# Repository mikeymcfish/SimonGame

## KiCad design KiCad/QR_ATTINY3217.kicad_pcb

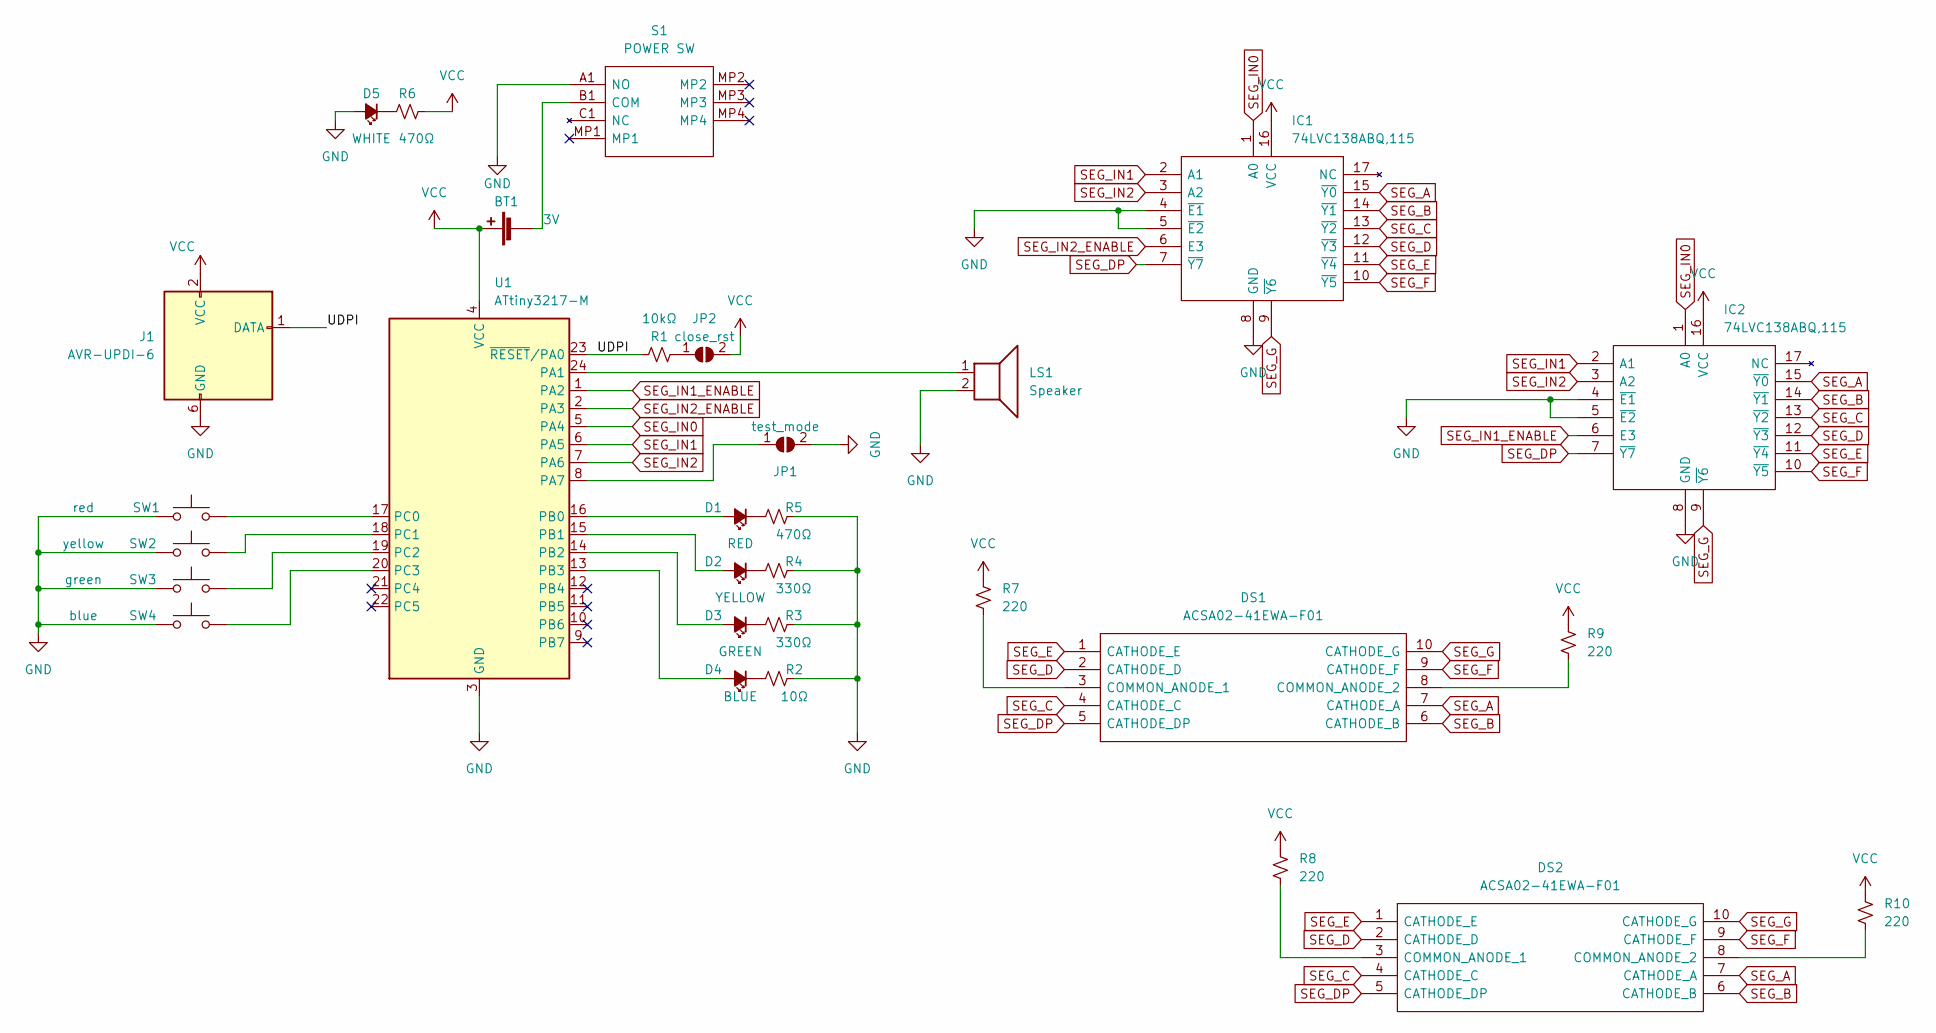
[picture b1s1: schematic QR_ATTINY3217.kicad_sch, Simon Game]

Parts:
BT1: 3V; SMTU2032LF
D1: RED; LED_1206_3216Metric_Pad1.42x1.75mm_HandSolder
D2: YELLOW; LED_1206_3216Metric_Pad1.42x1.75mm_HandSolder
D3: GREEN; LED_1206_3216Metric_Pad1.42x1.75mm_HandSolder
D4: BLUE; LED_1206_3216Metric_Pad1.42x1.75mm_HandSolder
D5: WHITE; LED_1206_3216Metric_Pad1.42x1.75mm_HandSolder
DS1, DS2: ACSA02-41EWA-F01; ACSA0241EWAF01; Mouser Part Number 604-ACSA02-41EWA
IC1, IC2: 74LVC138ABQ,115; 74AHCT595BQ115; Mouser Part Number 771-LVC138ABQ115
J1: AVR-UPDI-6; PinHeader_2x03_P2.54mm_Horizontal
JP1: test_mode; SolderJumper-2_P1.3mm_Open_Pad1.0x1.5mm
JP2: close_rst; SolderJumper-2_P1.3mm_Open_Pad1.0x1.5mm
LS1: Speaker; CPT111783SMTTR
R1: 10kΩ; R_1206_3216Metric_Pad1.30x1.75mm_HandSolder
R2: 10Ω; R_1206_3216Metric_Pad1.30x1.75mm_HandSolder
R3, R4: 330Ω; R_1206_3216Metric_Pad1.30x1.75mm_HandSolder
R5, R6: 470Ω; R_1206_3216Metric_Pad1.30x1.75mm_HandSolder
R7, R8, R9, R10: 220; R_1206_3216Metric
S1: POWER SW; MSS3VTR; Mouser Part Number 113-MSS3-V-T/R
SW1: red; FSM4JSMATR
SW2: yellow; FSM4JSMATR
SW3: green; FSM4JSMATR
SW4: blue; FSM4JSMATR
U1: ATtiny3217-M; QFN-24-1EP_4x4mm_P0.5mm_EP2.6x2.6mm

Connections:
/UDPI: J1.1 (DATA), R1.2, U1.23 (~RESET/PA0)
GND: D5.2 (A), IC1.4 (~E1), IC1.5 (~E2), IC1.8 (GND), IC2.4 (~E1), IC2.5 (~E2), IC2.8 (GND), J1.6 (GND), JP1.2 (B), LS1.2, R2.1, R3.2, R4.2, R5.2, S1.A1 (NO), SW1.4 (1), SW2.4 (1), SW3.4 (1), SW4.4 (1), U1.3 (GND), U1.25 (GND)
unnamed: BT1.2 (-), S1.B1 (COM)
unnamed: D1.1 (K), R5.1
unnamed: D1.2 (A), U1.16 (PB0)
unnamed: D2.1 (K), R4.1
unnamed: D2.2 (A), U1.15 (PB1)
unnamed: D3.1 (K), R3.1
unnamed: D3.2 (A), U1.14 (PB2)
unnamed: D4.1 (K), R2.2
unnamed: D4.2 (A), U1.13 (PB3)
unnamed: D5.1 (K), R6.2
unnamed: DS1.3 (COMMON_ANODE_1), R7.2
unnamed: DS1.8 (COMMON_ANODE_2), R9.2
unnamed: DS2.3 (COMMON_ANODE_1), R8.2
unnamed: DS2.8 (COMMON_ANODE_2), R10.2
unnamed: JP1.1 (A), U1.8 (PA7)
unnamed: JP2.1 (A), R1.1
unnamed: LS1.1, U1.24 (PA1)
unnamed: SW1.1, U1.17 (PC0)
unnamed: SW2.1 (2), U1.18 (PC1)
unnamed: SW3.1 (2), U1.19 (PC2)
unnamed: SW4.1 (2), U1.20 (PC3)
SEG_A: DS1.7 (CATHODE_A), DS2.7 (CATHODE_A), IC1.15 (~Y0), IC2.15 (~Y0)
SEG_B: DS1.6 (CATHODE_B), DS2.6 (CATHODE_B), IC1.14 (~Y1), IC2.14 (~Y1)
SEG_C: DS1.4 (CATHODE_C), DS2.4 (CATHODE_C), IC1.13 (~Y2), IC2.13 (~Y2)
SEG_D: DS1.2 (CATHODE_D), DS2.2 (CATHODE_D), IC1.12 (~Y3), IC2.12 (~Y3)
SEG_DP: DS1.5 (CATHODE_DP), DS2.5 (CATHODE_DP), IC1.7 (~Y7), IC2.7 (~Y7)
SEG_E: DS1.1 (CATHODE_E), DS2.1 (CATHODE_E), IC1.11 (~Y4), IC2.11 (~Y4)
SEG_F: DS1.9 (CATHODE_F), DS2.9 (CATHODE_F), IC1.10 (~Y5), IC2.10 (~Y5)
SEG_G: DS1.10 (CATHODE_G), DS2.10 (CATHODE_G), IC1.9 (~Y6), IC2.9 (~Y6)
SEG_IN0: IC1.1 (A0), IC2.1 (A0), U1.5 (PA4)
SEG_IN1: IC1.2 (A1), IC2.2 (A1), U1.6 (PA5)
SEG_IN1_ENABLE: IC2.6 (E3), U1.1 (PA2)
SEG_IN2: IC1.3 (A2), IC2.3 (A2), U1.7 (PA6)
SEG_IN2_ENABLE: IC1.6 (E3), U1.2 (PA3)
VCC: BT1.1 (+), IC1.16 (VCC), IC2.16 (VCC), J1.2 (VCC), JP2.2 (B), R6.1, R7.1, R8.1, R9.1, R10.1, U1.4 (VCC)

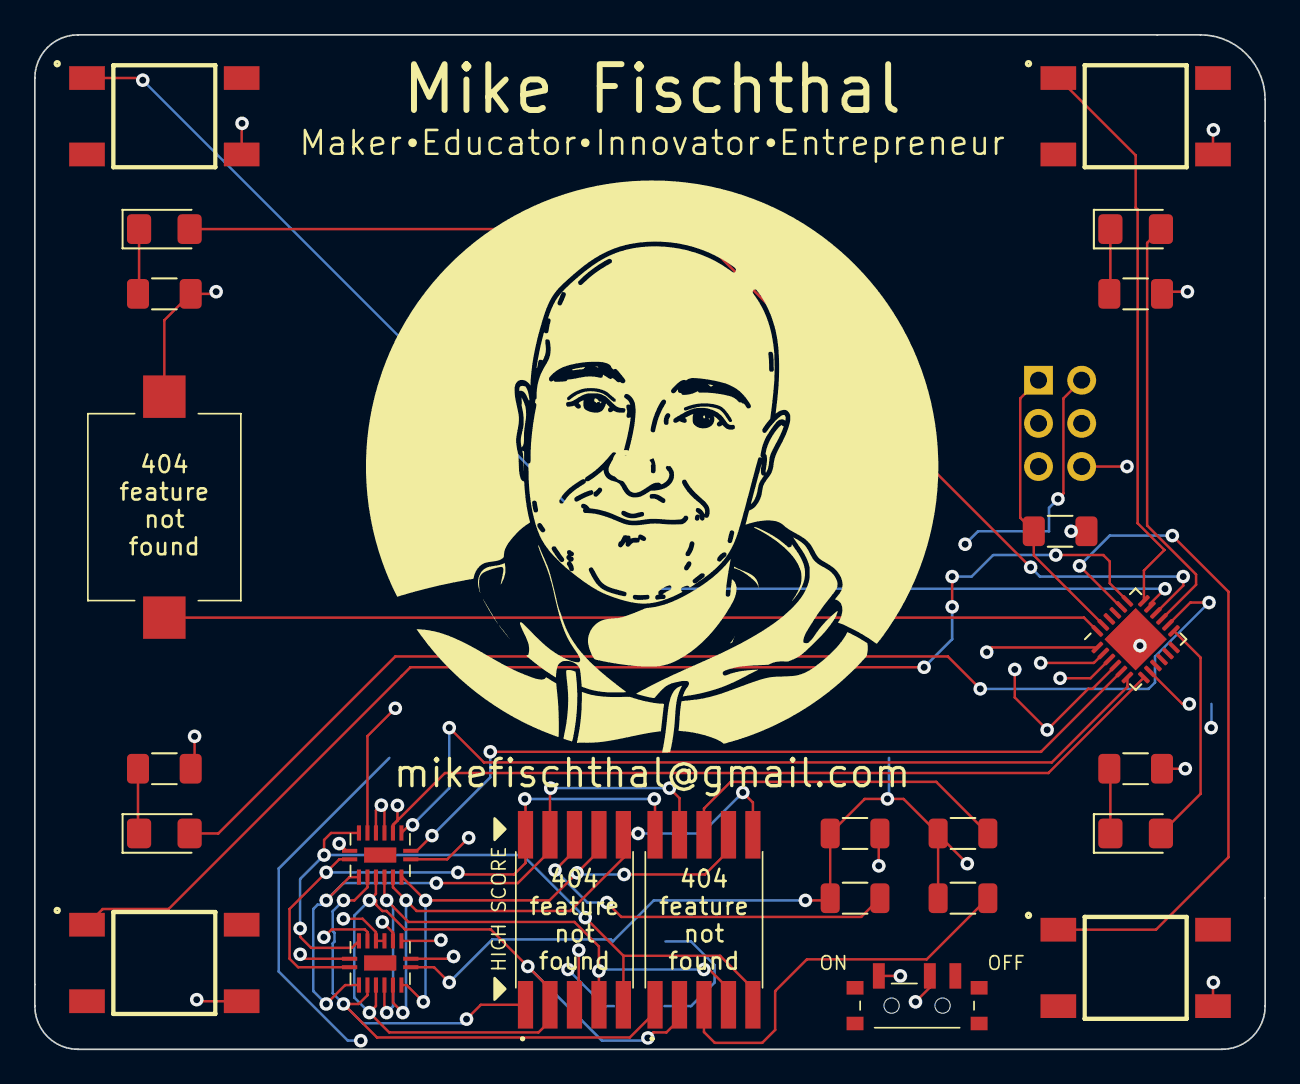
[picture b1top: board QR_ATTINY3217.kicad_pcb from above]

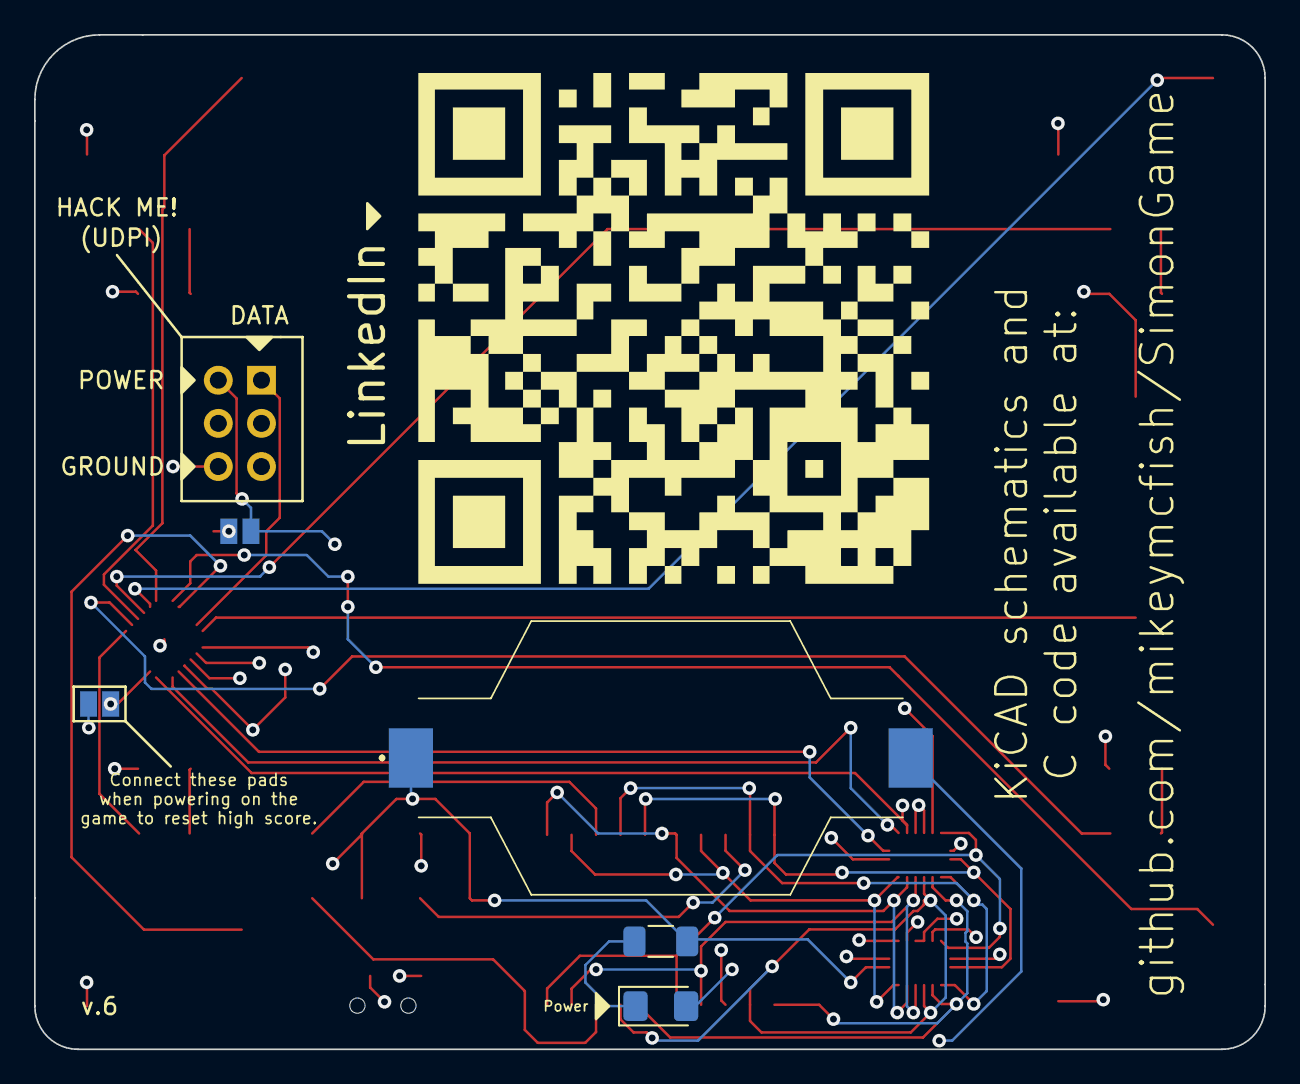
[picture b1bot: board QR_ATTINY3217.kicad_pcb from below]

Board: 4 copper layers, 72.4 x 59.7 mm, 30 parts (5 on the bottom side), 37 nets.

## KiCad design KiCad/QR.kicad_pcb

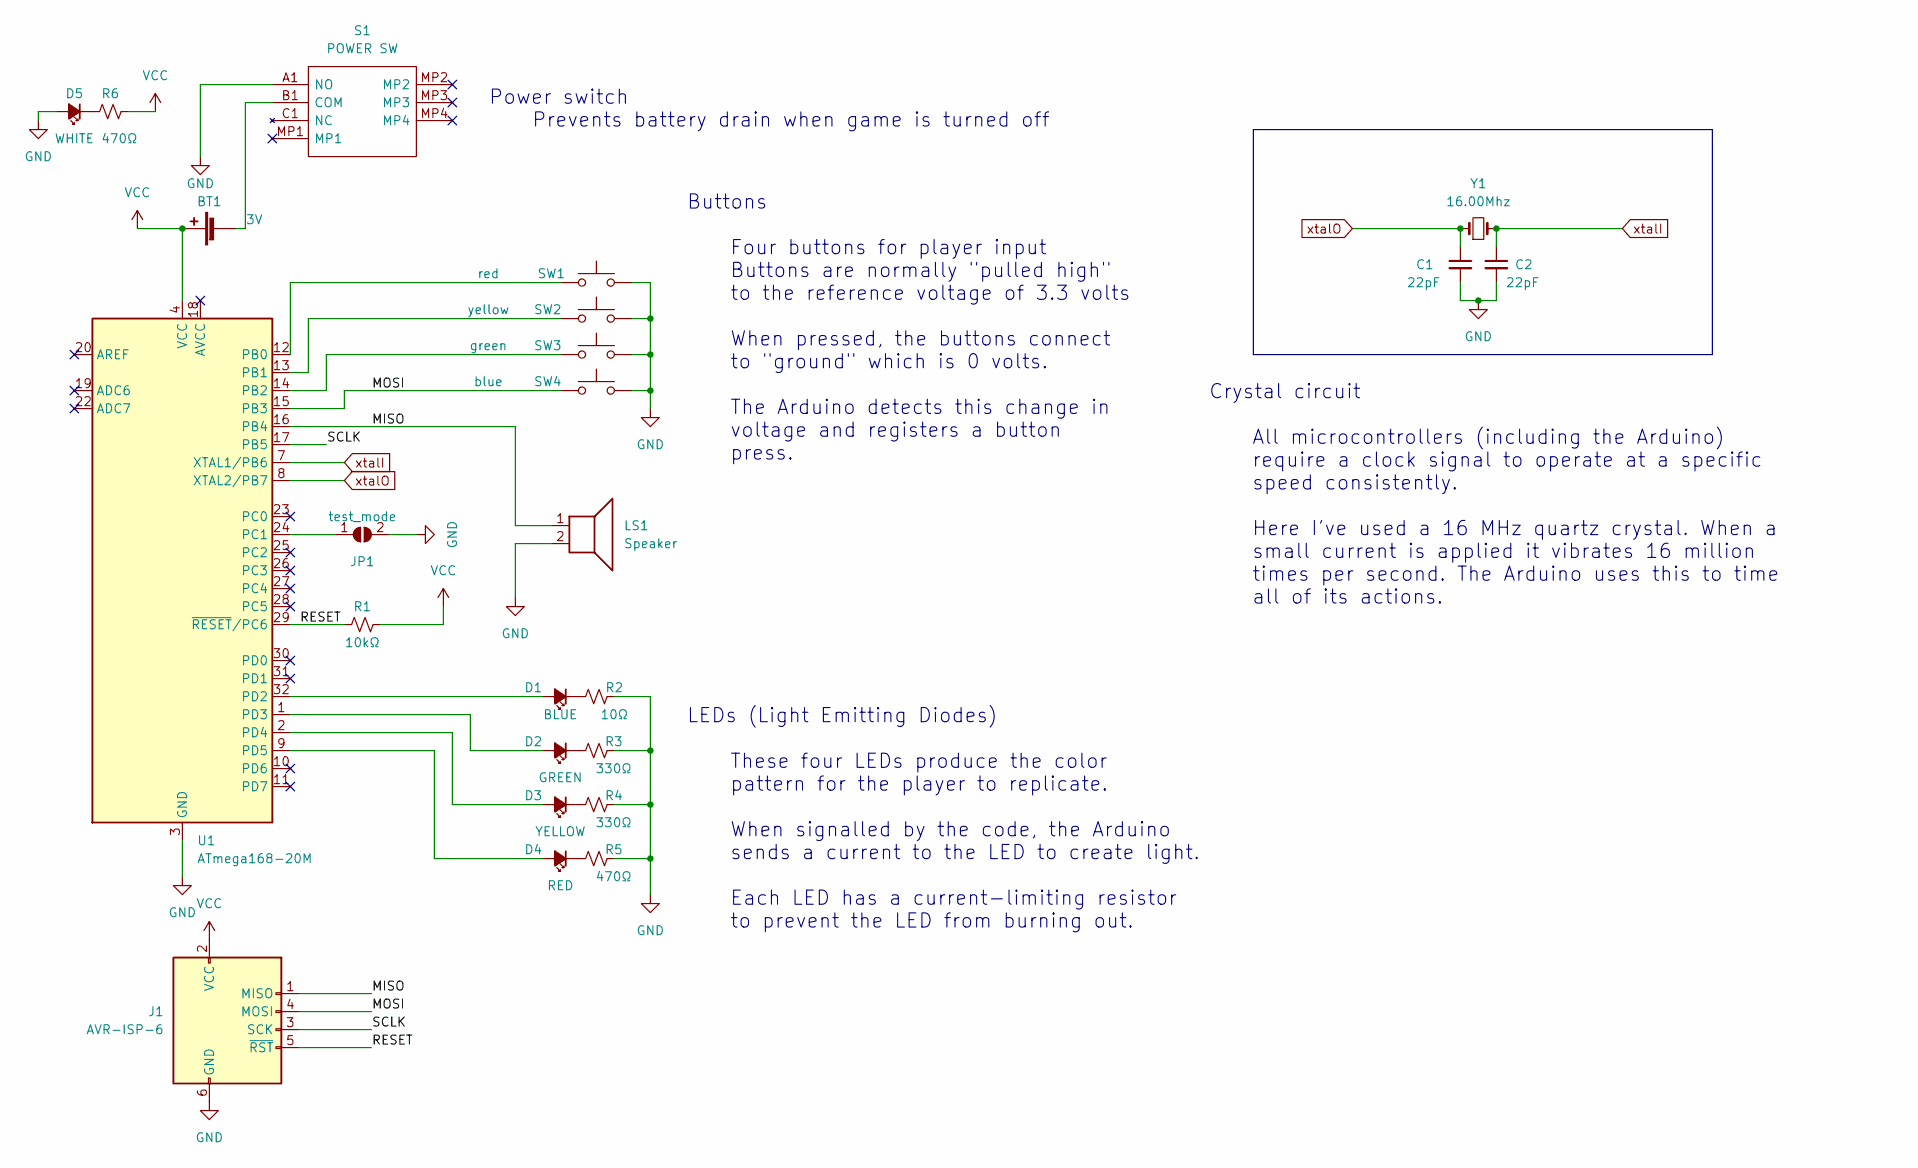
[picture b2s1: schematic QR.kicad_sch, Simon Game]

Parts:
BT1: 3V; SMTU2032LF
C1, C2: 22pF; C_1206_3216Metric_Pad1.33x1.80mm_HandSolder
D1: BLUE; LED_1206_3216Metric_Pad1.42x1.75mm_HandSolder
D2: GREEN; LED_1206_3216Metric_Pad1.42x1.75mm_HandSolder
D3: YELLOW; LED_1206_3216Metric_Pad1.42x1.75mm_HandSolder
D4: RED; LED_1206_3216Metric_Pad1.42x1.75mm_HandSolder
D5: WHITE; LED_1206_3216Metric_Pad1.42x1.75mm_HandSolder
J1: AVR-ISP-6; PinHeader_2x03_P2.54mm_Horizontal
JP1: test_mode; SolderJumper-2_P1.3mm_Open_Pad1.0x1.5mm
LS1: Speaker; CPT111783SMTTR
R1: 10kΩ; R_1206_3216Metric_Pad1.30x1.75mm_HandSolder
R2: 10Ω; R_1206_3216Metric_Pad1.30x1.75mm_HandSolder
R3, R4: 330Ω; R_1206_3216Metric_Pad1.30x1.75mm_HandSolder
R5, R6: 470Ω; R_1206_3216Metric_Pad1.30x1.75mm_HandSolder
S1: POWER SW; MSS3VTR; Mouser Part Number 113-MSS3-V-T/R
SW1: red; FSM4JSMATR
SW2: yellow; FSM4JSMATR
SW3: green; FSM4JSMATR
SW4: blue; FSM4JSMATR
U1: ATmega168-20M; QFN-32-1EP_5x5mm_P0.5mm_EP3.1x3.1mm
Y1: 16.00Mhz; Crystal_SMD_HC49-SD_HandSoldering

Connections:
/MISO: J1.1 (MISO), LS1.1, U1.16 (PB4)
/MOSI: J1.4 (MOSI), SW4.1, U1.15 (PB3)
/RESET: J1.5 (~RST), R1.2, U1.29 (~RESET/PC6)
/SCLK: J1.3 (SCK), U1.17 (PB5)
GND: C1.2, C2.2, D5.2 (A), J1.6 (GND), JP1.2 (B), LS1.2, R2.1, R3.2, R4.2, R5.2, S1.A1 (NO), SW1.4 (2), SW2.4 (2), SW3.4 (2), SW4.4 (2), U1.3 (GND), U1.5 (GND), U1.21 (GND), U1.33 (GND); also elsewhere on the board
unnamed: BT1.2 (-), S1.B1 (COM)
unnamed: D1.1 (K), R2.2
unnamed: D1.2 (A), U1.32 (PD2)
unnamed: D2.1 (K), R3.1
unnamed: D2.2 (A), U1.1 (PD3)
unnamed: D3.1 (K), R4.1
unnamed: D3.2 (A), U1.2 (PD4)
unnamed: D4.1 (K), R5.1
unnamed: D4.2 (A), U1.9 (PD5)
unnamed: D5.1 (K), R6.2
unnamed: SW1.1, U1.12 (PB0)
unnamed: SW2.1, U1.13 (PB1)
unnamed: SW3.1, U1.14 (PB2)
unnamed 18: JP1.1 (A), U1.24 (PC1); also elsewhere on the board
VCC: BT1.1 (+), J1.2 (VCC), R1.1, R6.1, U1.4 (VCC), U1.6 (VCC)
xtalI: C2.1, U1.7 (XTAL1/PB6), Y1.2
xtalO: C1.1, U1.8 (XTAL2/PB7), Y1.1

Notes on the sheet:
Buttons Four buttons for player input Buttons are normally "pulled high" to the reference voltage of 3.3 volts When pressed, the buttons connect to "ground" which is 0 volts. The Arduino detects this change in voltage and registers a button press.
LEDs (Light Emitting Diodes) These four LEDs produce the color pattern for the player to replicate. When signalled by the code, the Arduino sends a current to the LED to create light. Each LED has a current-limiting resistor to prevent the LED from burning out.
Power switch Prevents battery drain when game is turned off
Crystal circuit All microcontrollers (including the Arduino) require a clock signal to operate at a specific speed consistently. Here I've used a 16 MHz quartz crystal. When a small current is applied it vibrates 16 million times per second. The Arduino uses this to time all of its actions.

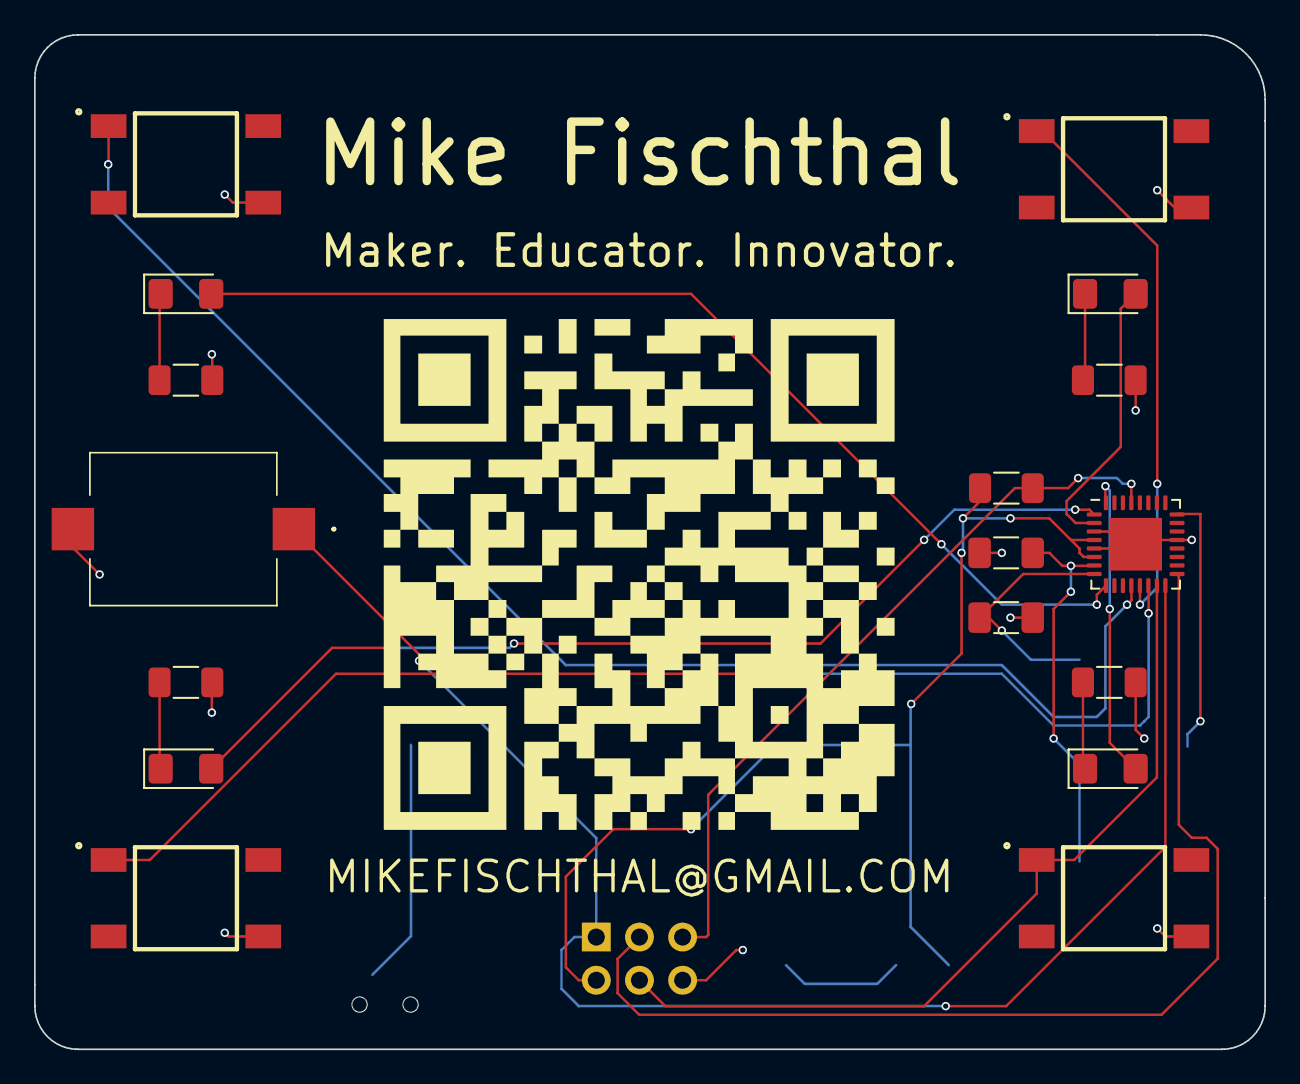
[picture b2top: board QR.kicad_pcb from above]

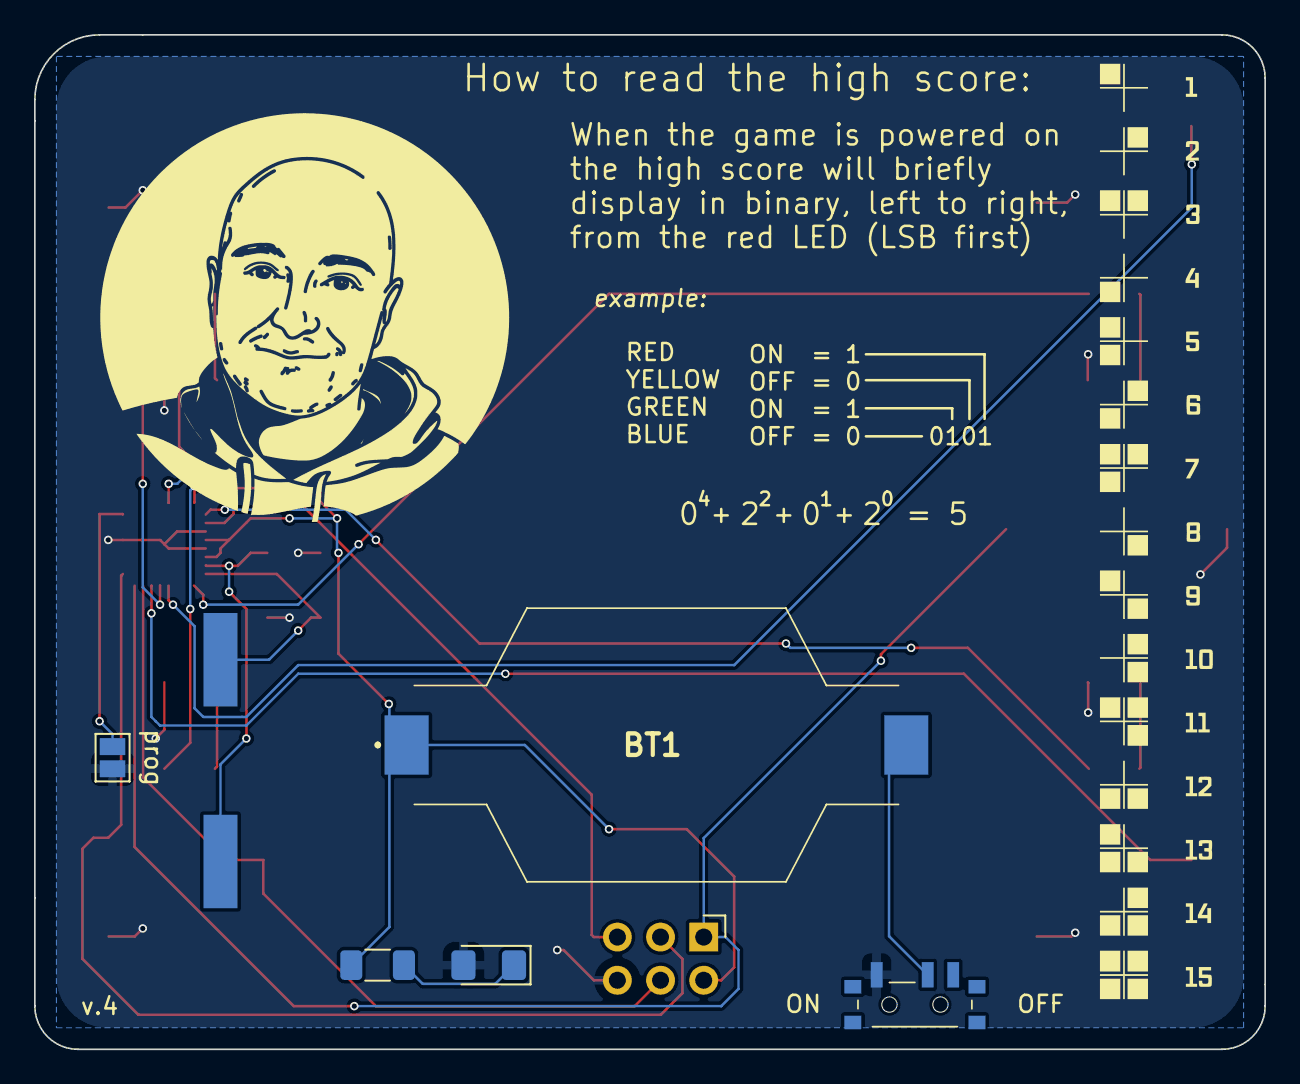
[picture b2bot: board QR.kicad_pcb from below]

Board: 2 copper layers, 72.4 x 59.7 mm, 24 parts (7 on the bottom side), 22 nets.

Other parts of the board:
prog: test_mode; SolderJumper-2_P1.3mm_Open_Pad1.0x1.5mm

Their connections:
GND: prog.2 (B); also elsewhere on the board
unnamed 18: prog.1 (A); also elsewhere on the board

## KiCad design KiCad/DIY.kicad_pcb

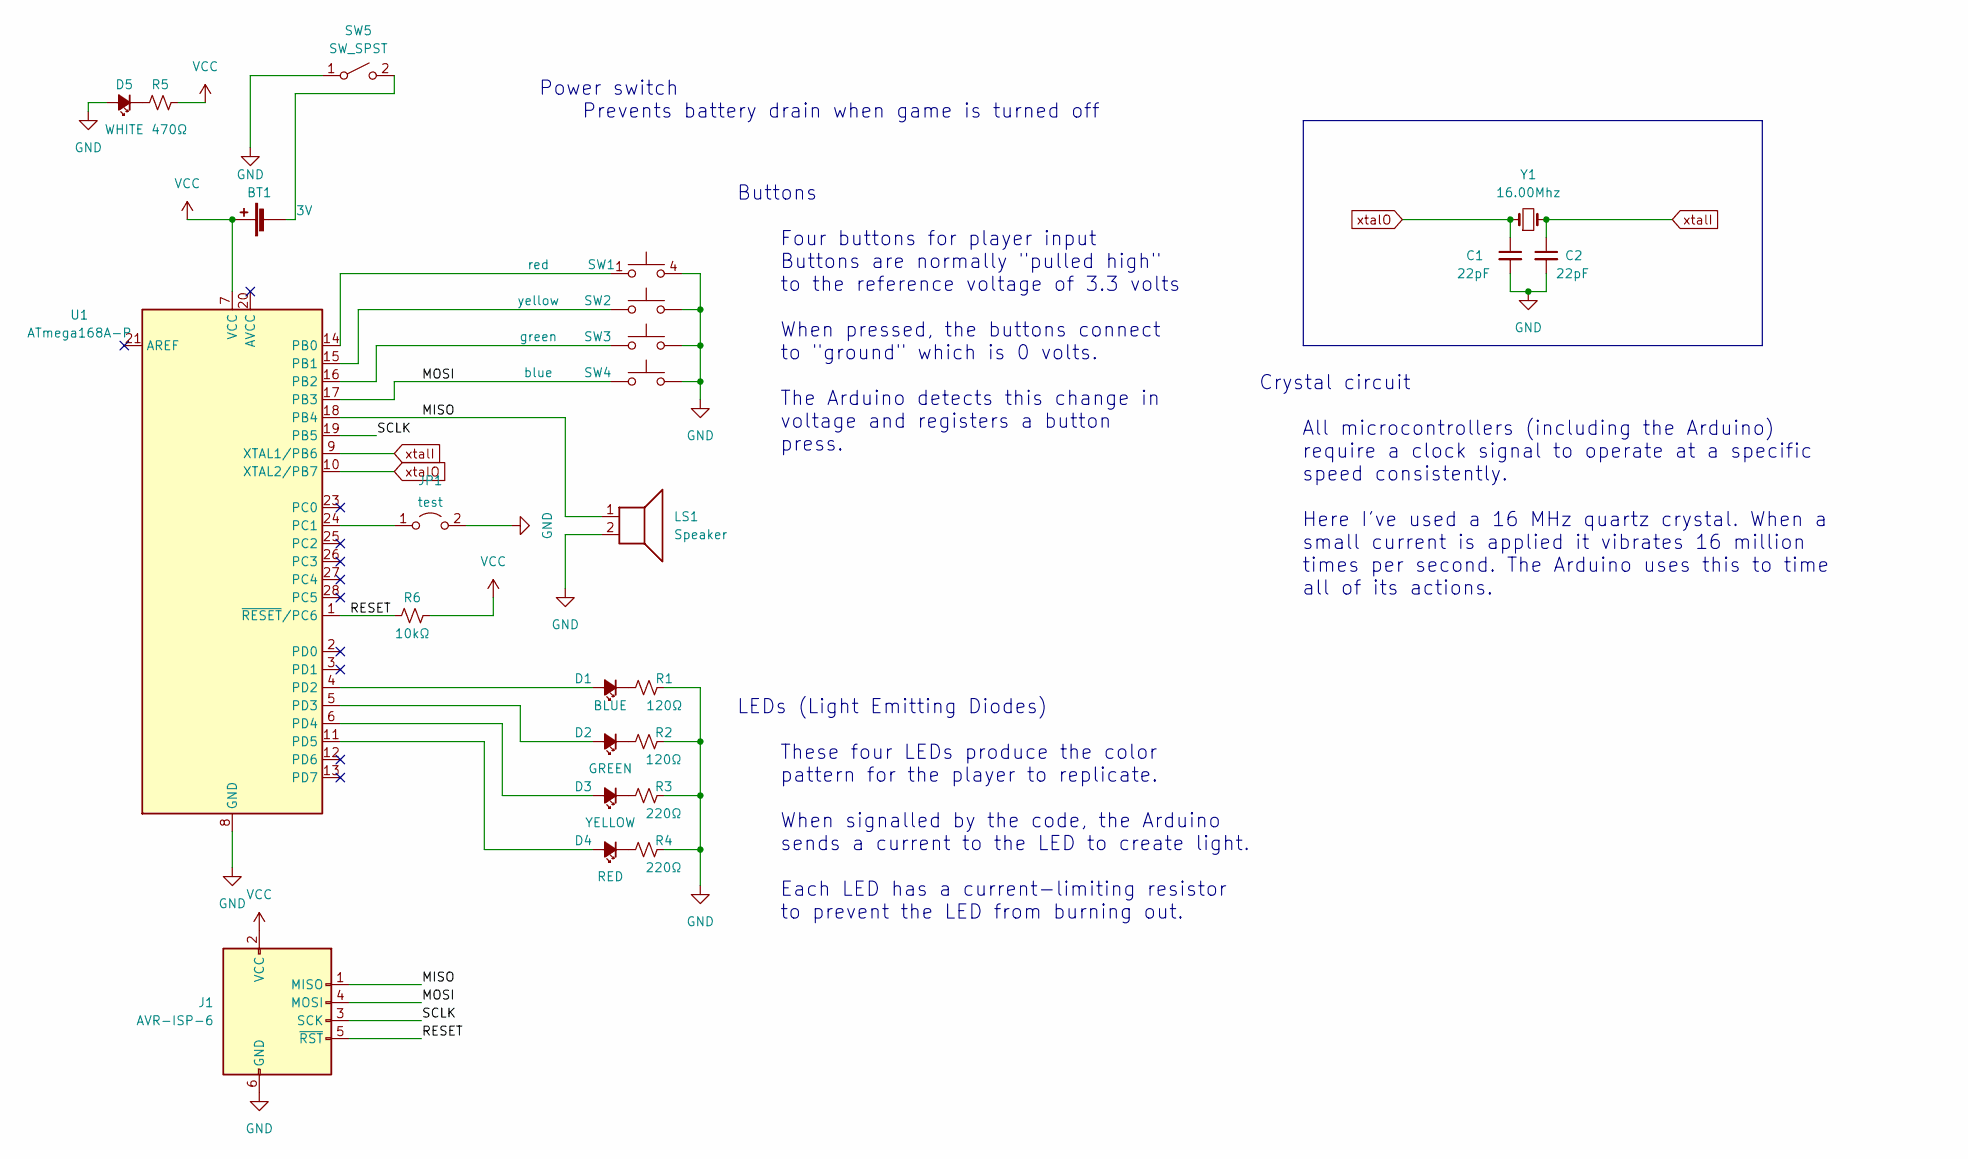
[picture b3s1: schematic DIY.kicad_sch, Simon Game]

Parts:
BT1: 3V; SMTU2032LF
C1, C2: 22pF; C_Disc_D7.5mm_W5.0mm_P5.00mm
D1: BLUE; LED_D5.0mm
D2: GREEN; LED_D5.0mm
D3: YELLOW; LED_D5.0mm
D4: RED; LED_D5.0mm
D5: WHITE; LED_D5.0mm
J1: AVR-ISP-6; IDC-Header_2x03_P2.54mm_Vertical
JP1: test; PinHeader_1x02_P2.54mm_Vertical
LS1: Speaker; PKM13EPYH4002-B0
R1, R2: 120Ω; R_Axial_DIN0207_L6.3mm_D2.5mm_P10.16mm_Horizontal
R3, R4: 220Ω; R_Axial_DIN0207_L6.3mm_D2.5mm_P10.16mm_Horizontal
R5: 470Ω; R_Axial_DIN0207_L6.3mm_D2.5mm_P10.16mm_Horizontal
R6: 10kΩ; R_Axial_DIN0207_L6.3mm_D2.5mm_P10.16mm_Horizontal
SW1: red; SW_PUSH_6mm
SW2: yellow; SW_PUSH_6mm
SW3: green; SW_PUSH_6mm
SW4: blue; SW_PUSH_6mm
SW5: SW_SPST; SW_DIP_SPSTx01_Slide_9.78x4.72mm_W7.62mm_P2.54mm
U1: ATmega168A-P; DIP-28_W7.62mm
Y1: 16.00Mhz; Crystal_HC52-6mm_Vertical

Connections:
/MISO: J1.1 (MISO), LS1.1, U1.18 (PB4)
/MOSI: J1.4 (MOSI), SW4.1, U1.17 (PB3)
/RESET: J1.5 (~RST), R6.2, U1.1 (~RESET/PC6)
/SCLK: J1.3 (SCK), U1.19 (PB5)
GND: C1.2, C2.2, D5.2 (A), J1.6 (GND), JP1.2 (B), LS1.2, R1.1, R2.2, R3.2, R4.2, SW1.4 (2), SW2.4 (2), SW3.4 (2), SW4.4 (2), SW5.1 (A), U1.8 (GND), U1.22 (GND)
unnamed: BT1.2 (-), SW5.2 (B)
unnamed: D1.1 (K), R1.2
unnamed: D1.2 (A), U1.4 (PD2)
unnamed: D2.1 (K), R2.1
unnamed: D2.2 (A), U1.5 (PD3)
unnamed: D3.1 (K), R3.1
unnamed: D3.2 (A), U1.6 (PD4)
unnamed: D4.1 (K), R4.1
unnamed: D4.2 (A), U1.11 (PD5)
unnamed: D5.1 (K), R5.2
unnamed: JP1.1 (A), U1.24 (PC1)
unnamed: SW1.1, U1.14 (PB0)
unnamed: SW2.1, U1.15 (PB1)
unnamed: SW3.1, U1.16 (PB2)
VCC: BT1.1 (+), J1.2 (VCC), R5.1, R6.1, U1.7 (VCC)
xtalI: C2.1, U1.9 (XTAL1/PB6), Y1.2
xtalO: C1.1, U1.10 (XTAL2/PB7), Y1.1

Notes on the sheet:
Buttons Four buttons for player input Buttons are normally "pulled high" to the reference voltage of 3.3 volts When pressed, the buttons connect to "ground" which is 0 volts. The Arduino detects this change in voltage and registers a button press.
LEDs (Light Emitting Diodes) These four LEDs produce the color pattern for the player to replicate. When signalled by the code, the Arduino sends a current to the LED to create light. Each LED has a current-limiting resistor to prevent the LED from burning out.
Power switch Prevents battery drain when game is turned off
Crystal circuit All microcontrollers (including the Arduino) require a clock signal to operate at a specific speed consistently. Here I've used a 16 MHz quartz crystal. When a small current is applied it vibrates 16 million times per second. The Arduino uses this to time all of its actions.

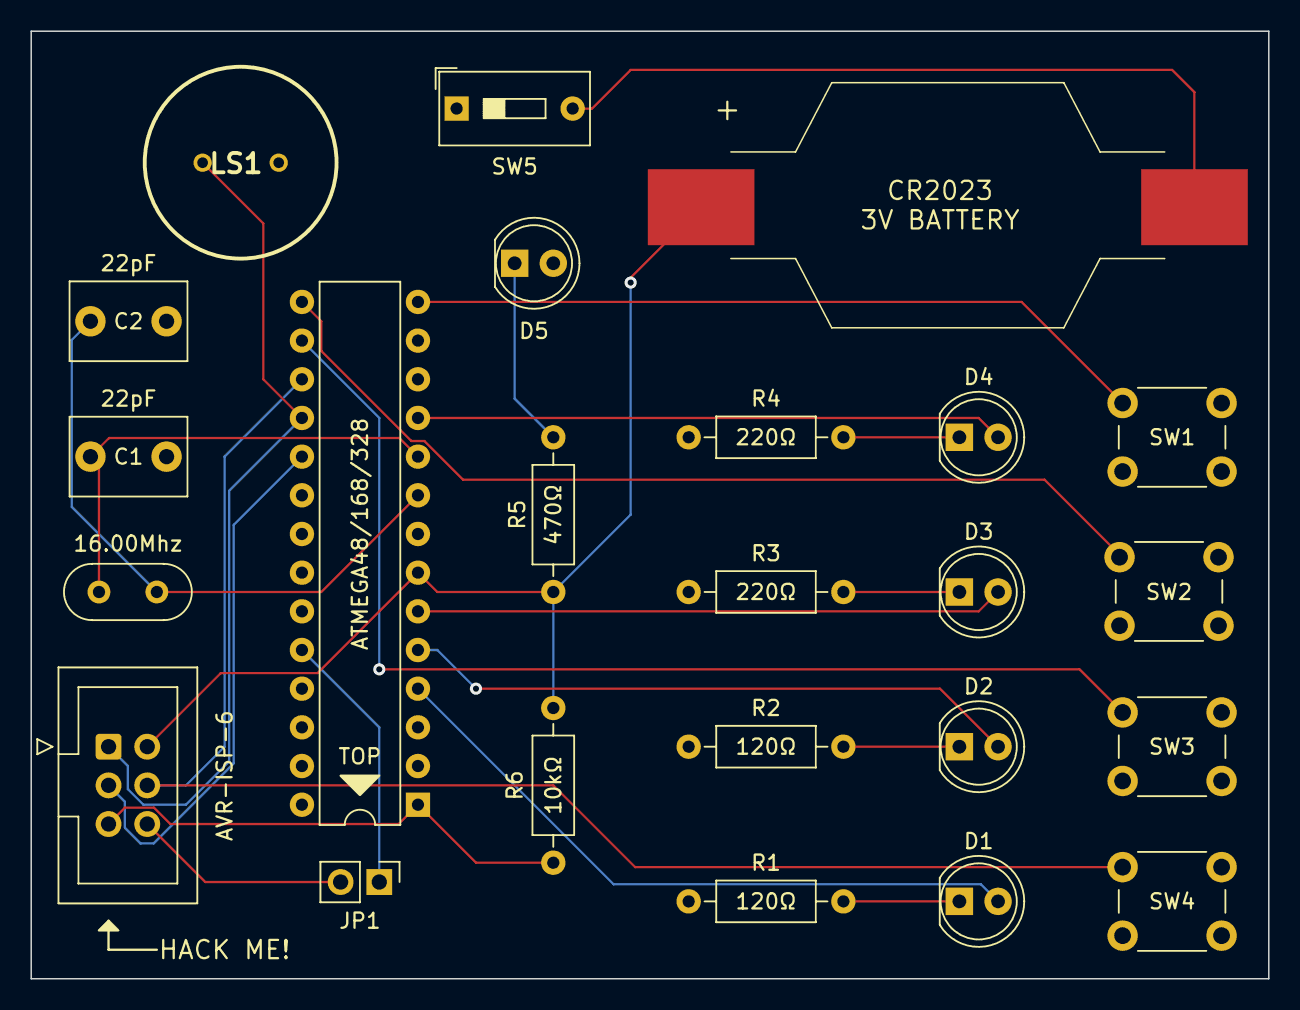
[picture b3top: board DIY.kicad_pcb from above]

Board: 2 copper layers, 81.3 x 62.2 mm, 24 parts (0 on the bottom side), 22 nets.

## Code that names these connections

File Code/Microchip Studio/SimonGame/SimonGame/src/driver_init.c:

/**
 * \file
 *
 * \brief Driver initialization.
 *
 (c) 2020 Microchip Technology Inc. and its subsidiaries.

    Subject to your compliance with these terms,you may use this software and
    any derivatives exclusively with Microchip products.It is your responsibility
    to comply with third party license terms applicable to your use of third party
    software (including open source software) that may accompany Microchip software.

    THIS SOFTWARE IS SUPPLIED BY MICROCHIP "AS IS". NO WARRANTIES, WHETHER
    EXPRESS, IMPLIED OR STATUTORY, APPLY TO THIS SOFTWARE, INCLUDING ANY IMPLIED
    WARRANTIES OF NON-INFRINGEMENT, MERCHANTABILITY, AND FITNESS FOR A
    PARTICULAR PURPOSE.

    IN NO EVENT WILL MICROCHIP BE LIABLE FOR ANY INDIRECT, SPECIAL, PUNITIVE,
    INCIDENTAL OR CONSEQUENTIAL LOSS, DAMAGE, COST OR EXPENSE OF ANY KIND
    WHATSOEVER RELATED TO THE SOFTWARE, HOWEVER CAUSED, EVEN IF MICROCHIP HAS
    BEEN ADVISED OF THE POSSIBILITY OR THE DAMAGES ARE FORESEEABLE. TO THE
    FULLEST EXTENT ALLOWED BY LAW, MICROCHIP'S TOTAL LIABILITY ON ALL CLAIMS IN
    ANY WAY RELATED TO THIS SOFTWARE WILL NOT EXCEED THE AMOUNT OF FEES, IF ANY,
    THAT YOU HAVE PAID DIRECTLY TO MICROCHIP FOR THIS SOFTWARE.
 *
 */

/*
 * Code generated by START.
 *
 * This file will be overwritten when reconfiguring your START project.
 * Please copy examples or other code you want to keep to a separate file
 * to avoid losing it when reconfiguring.
 */

#include "driver_init.h"
#include <system.h>

/**
 * \brief System initialization
 */
void system_init()
{
	mcu_init();

	/* PORT setting on PA1 */

	// Set pin direction to output

	SPEAKER_set_level(
	    // <y> Initial level
	    // <id> pad_initial_level
	    // <false"> Low
	    // <true"> High
	    false);

	SPEAKER_set_dir(PORT_DIR_OUT);

	/* PORT setting on PA2 */

	// Set pin direction to output

	SEG0EN_set_level(
	    // <y> Initial level
	    // <id> pad_initial_level
	    // <false"> Low
	    // <true"> High
	    false);

	SEG0EN_set_dir(PORT_DIR_OUT);

	/* PORT setting on PA3 */

	// Set pin direction to output

	SEG1EN_set_level(
	    // <y> Initial level
	    // <id> pad_initial_level
	    // <false"> Low
	    // <true"> High
	    false);

	SEG1EN_set_dir(PORT_DIR_OUT);

	/* PORT setting on PA4 */

	// Set pin direction to output

	SEG0_set_level(
	    // <y> Initial level
	    // <id> pad_initial_level
	    // <false"> Low
	    // <true"> High
	    false);

	SEG0_set_dir(PORT_DIR_OUT);

	/* PORT setting on PA5 */

	// Set pin direction to output

	SEG1_set_level(
	    // <y> Initial level
	    // <id> pad_initial_level
	    // <false"> Low
	    // <true"> High
	    false);

	SEG1_set_dir(PORT_DIR_OUT);

	/* PORT setting on PA6 */

	// Set pin direction to output

	SEG2_set_level(
	    // <y> Initial level
	    // <id> pad_initial_level
	    // <false"> Low
	    // <true"> High
	    false);

	SEG2_set_dir(PORT_DIR_OUT);

	/* PORT setting on PB0 */

	// Set pin direction to output

	LED_R_set_level(
	    // <y> Initial level
	    // <id> pad_initial_level
	    // <false"> Low
	    // <true"> High
	    false);

	LED_R_set_dir(PORT_DIR_OUT);

	/* PORT setting on PB1 */

	// Set pin direction to output

	LED_Y_set_level(
	    // <y> Initial level
	    // <id> pad_initial_level
	    // <false"> Low
	    // <true"> High
	    false);

	LED_Y_set_dir(PORT_DIR_OUT);

	/* PORT setting on PB2 */

	// Set pin direction to output

	LED_G_set_level(
	    // <y> Initial level
	    // <id> pad_initial_level
	    // <false"> Low
	    // <true"> High
	    false);

	LED_G_set_dir(PORT_DIR_OUT);

	/* PORT setting on PB3 */

	// Set pin direction to output

	LED_B_set_level(
	    // <y> Initial level
	    // <id> pad_initial_level
	    // <false"> Low
	    // <true"> High
	    false);

	LED_B_set_dir(PORT_DIR_OUT);

	/* PORT setting on PC0 */

	// Set pin direction to input
	BTN_R_set_dir(PORT_DIR_IN);

	BTN_R_set_pull_mode(
	    // <y> Pull configuration
	    // <id> pad_pull_config
	    // <PORT_PULL_OFF"> Off
	    // <PORT_PULL_UP"> Pull-up
	    PORT_PULL_UP);

	/* PORT setting on PC1 */

	// Set pin direction to input
	BTN_Y_set_dir(PORT_DIR_IN);

	BTN_Y_set_pull_mode(
	    // <y> Pull configuration
	    // <id> pad_pull_config
	    // <PORT_PULL_OFF"> Off
	    // <PORT_PULL_UP"> Pull-up
	    PORT_PULL_UP);

	/* PORT setting on PC2 */

	// Set pin direction to input
	BTN_G_set_dir(PORT_DIR_IN);

	BTN_G_set_pull_mode(
	    // <y> Pull configuration
	    // <id> pad_pull_config
	    // <PORT_PULL_OFF"> Off
	    // <PORT_PULL_UP"> Pull-up
	    PORT_PULL_UP);

	/* PORT setting on PC3 */

	// Set pin direction to input
	BTN_B_set_dir(PORT_DIR_IN);

	BTN_B_set_pull_mode(
	    // <y> Pull configuration
	    // <id> pad_pull_config
	    // <PORT_PULL_OFF"> Off
	    // <PORT_PULL_UP"> Pull-up
	    PORT_PULL_UP);

	CLKCTRL_init();

	CPUINT_init();

	SLPCTRL_init();

	BOD_init();
}

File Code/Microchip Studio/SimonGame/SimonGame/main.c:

#include <atmel_start.h>
#include <util/delay.h>
#include <avr/eeprom.h>
#include <avr/io.h>
#include <stdio.h>
#include <stdlib.h>
#include <time.h>
#include <string.h>
#include <organ.h>
#include <scale16.h>
#include <avr/eeprom.h>

#define NOTE_C2  65
#define NOTE_CS3 139
#define NOTE_G3  196
#define NOTE_A3  220
#define NOTE_B3  247
#define NOTE_C4  262
#define NOTE_D4  294
#define NOTE_D5  587
#define NOTE_A4  440
#define NOTE_F4  349
#define NOTE_DURATION 0xF000
#define SCORE_ADDRESS 0x1400

#define A 0
#define B 0b01000000
#define C 0b00100000
#define D 0b01100000
#define E 0b00010000
#define F 0b01010000
#define G 0b00110000
#define P 0b01110000

#define NUM0 0x3F
#define NUM1 0x06
#define NUM2 0x5B
#define NUM3 0x4F
#define NUM4 0x66
#define NUM5 0x6D
#define NUM6 0x7D
#define NUM7 0x07
#define NUM8 0x7F
#define NUM9 0x6F 
#define ENABLE (1 << 2)

#define DEL 50

#define LOOP_COUNT 1200

#define TEST_MODE 15

/*

PB[0:3] LEDS (R, Y, G, B) 
PC[0:3] BUTTONS (R, Y, G, B)
PA0 UDPI
PA1 SPEAKER
PA2 SEG0EN
PA3 SEG1EN
PA4 SEG0
PA5 SEG1
PA6 SEG2

*/
bool hold_display = 1;

char sequence[20] = {};
char currLight = 0;
char lightCount = 0;
char sizeQ = 0;
int speed = 400;
bool waitForInput = 0;
bool isMatch = 0;

uint8_t testThing = 1;

// change this with ADC:
int psuedo = 14;

void displayNumber(int NUM) {
	
	PORTA_OUT = 0; 
	
	for (int i = 0; i < LOOP_COUNT; i++) {
		
		NUM & 1 << 0 ? PORTA_OUT = ENABLE | A : 1;
		_delay_us(DEL);
		NUM & 1 << 1 ? PORTA_OUT = ENABLE | B : 1;
		_delay_us(DEL);
		NUM & 1 << 2 ? PORTA_OUT = ENABLE | C : 1;
		_delay_us(DEL);		
		NUM & 1 << 3 ? PORTA_OUT = ENABLE | D : 1;
		_delay_us(DEL);
		NUM & 1 << 4 ? PORTA_OUT = ENABLE | E : 1;
		_delay_us(DEL);
		NUM & 1 << 5 ? PORTA_OUT = ENABLE | F : 1;
		_delay_us(DEL);
		NUM & 1 << 6 ? PORTA_OUT = ENABLE | G : 1;
		_delay_us(DEL);
		PORTA_OUT &= 0b10001111;
	}
	PORTA_OUT &= 0b10000011; 
	
}

void lightLED (int i) {
	
	PORTB_OUT = 1 << i;
	switch (i)
	{
	case 0:
		playNote(B3,NOTE_DURATION);
		break;
	case 1:
		playNote(C4,NOTE_DURATION);
		break;
	case 2:
		playNote(D5,NOTE_DURATION);
		break;
	case 3:
		playNote(E6,NOTE_DURATION);
		break;
	
	}
	if (waitForInput)
		_delay_ms(200);
	else
		_delay_ms(600);
	PORTB_OUT = 0;
}
	
bool checkButton(char b) {
	char expectingButton = sequence[currLight];
	isMatch = (expectingButton==b);
	return isMatch;
}

void advanceOrEnd() {
	currLight++;
	if (currLight!=lightCount) {
		waitForInput=1;
		_delay_ms(10);
	}
	else {
		waitForInput=0;
	}
}

void addToSequence() {
	_delay_ms(100);
	int nextLight = (rand()%4);
	sequence[lightCount] = (char)nextLight;
	lightCount++;
}

void playSequence() {
	for(int i = 0; i < lightCount; i++ ) {
		char c = sequence[i];
		lightLED(c);
		_delay_ms(50);
	}
}

void endGame() {
	
	playNote(D4,(NOTE_DURATION));
	playNote(D4,(NOTE_DURATION));
	
	playNote(Cx3,NOTE_DURATION);
	playNote(Cx3,NOTE_DURATION);

	playNote(C2,NOTE_DURATION);
	playNote(C2,NOTE_DURATION);
	playNote(C2,NOTE_DURATION);

	updateHighScoreIfHigher();

	memset(sequence,'0',1);
	currLight = 0;
	waitForInput = 0;
	for (int i=0; i<20; i++) sequence[i]=0;
	lightCount = 0;
	_delay_ms(500);
	playSong();
}

void playSong() {
	
	playNote(D4,(NOTE_DURATION));
	
	playNote(A4,(NOTE_DURATION));
	
	playNote(F4,(NOTE_DURATION));
	
	playNote(D5,(NOTE_DURATION));
	playNote(D5,(NOTE_DURATION));
	
	playNote(F4,(NOTE_DURATION));
	
	playNote(D5,(NOTE_DURATION));
	playNote(D5,(NOTE_DURATION));
}

void updateHighScoreIfHigher() {

	uint8_t *location = (uint8_t *) 0;
	//eeprom_update_byte(location, 11);
	uint8_t score = eeprom_read_byte(location);
	uint8_t currScore = (uint8_t) --lightCount;
	if (currScore > score) 
		eeprom_update_byte(location,lightCount);
}

int main(void)
{
	atmel_start_init();
	PORTA_OUT = 0; 
	srand(psuedo);
	PORTB_OUT = 0x0F;  

//are there consistent segments that are more powerful? is it timing?
	 displayNumber(NUM0);
	 _delay_ms(100);
	 displayNumber(NUM1);
	 _delay_ms(100);
	 displayNumber(NUM2);
	 _delay_ms(100);
	 displayNumber(NUM3);
	 _delay_ms(100);
	 displayNumber(NUM4);
	 _delay_ms(100);
	 displayNumber(NUM5);
	 _delay_ms(100);
	 displayNumber(NUM6);
	 _delay_ms(100);
	 displayNumber(NUM7);
	 _delay_ms(100);
	 displayNumber(NUM8);
	 _delay_ms(100);
	 displayNumber(NUM9);
	 _delay_ms(100);
	 
	 //show high score
	PORTB_OUT = eeprom_read_byte( (uint8_t *) 0);
	_delay_ms(1200);
	PORTB_OUT = 0;
	_delay_ms(200);
		
	playSong();
		
	while (1) {			
		
		 if (!waitForInput) {
			 currLight = 0;
			 addToSequence();
			 playSequence();
			 waitForInput = 1;
		 }

		 if (!BTN_R_get_level()) 
		 {
			 lightLED(0);
			 _delay_ms(150);
			 checkButton(0) ? advanceOrEnd() : endGame();
		 }
		 
		 if (!BTN_Y_get_level())
		 {
			lightLED(1);
			_delay_ms(150);
			checkButton(1) ? advanceOrEnd() : endGame();

		 }
		 
		if (!BTN_G_get_level())
		{
			lightLED(2);
			_delay_ms(150);			
			checkButton(2) ? advanceOrEnd() : endGame();
		}
		  
		if (!BTN_B_get_level()) 
		{
			lightLED(3);
			_delay_ms(150);
			checkButton(3) ? advanceOrEnd() : endGame();

		}
			
	}
}

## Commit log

2022-04-18 Init
2022-04-21 DIY board
2022-04-23 buzzer update
2022-05-08 ATTINY version
2022-05-08 C Version
    *high score display not working
